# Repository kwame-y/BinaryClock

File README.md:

# TickTock — Pocket Binary Clock

A rechargeable pocket clock displaying **HH:MM:SS with 20 LEDs**, built around an ATtiny1616, a constant-current LED driver, and a real-time clock. Three edge-mounted buttons provide the planned MODE, PLUS, and MINUS controls, with USB-C for charging.

Designed in **KiCad 10**. This snapshot comes from **BinaryClock3**, with “TickTock REV 1.0” on the front silkscreen and a clock-face illustration on the back.

**Status: routed draft, not a manufacturing release.** The current checks report zero unconnected items and zero schematic-to-PCB parity issues, but electrical and design-rule violations remain. See [validation details](Hardware/VALIDATION.md).

## Schematic

The current schematic labels U4 as **BQ25186DLHR**. Its custom symbol and footprint identifiers still contain **BQ25185**; their suitability must be verified against the intended device before assembly. The earlier BQ24074 circuit is not included in this snapshot.

Open [Hardware/BinaryClock3.kicad_pro](Hardware/BinaryClock3.kicad_pro) in KiCad 10. Project-specific symbols, footprints, and available custom 3D models are included.

## Silkscreen

## PCB Layout

 · 

The saved board has **four copper layers** and a **1.6 mm thickness setting**. The plotted outline is approximately **60 × 30 mm**, larger than the original 50 × 30 mm target. Its saved appearance uses white front solder mask and blue back solder mask. The stackup currently specifies no copper finish; these settings need reconciliation with the intended manufacturing order.

The snapshot contains 334 track segments and 163 vias. These counts describe the saved design, not a fabrication approval.

## 3D Render

These are direct KiCad renders of the saved board. Some component bodies are absent because their 3D models are missing or unassigned; visible bare pads do not imply that those parts are omitted from the BOM.

## Bill of Materials

[Download BOM.csv](Production/BOM.csv), exported from the current schematic. It contains **52 component instances and 4 test points**. The external battery and thermistor are not included. Generic values and library names are not a complete purchasing specification; exact orderable parts, ratings, and pricing still need to be finalized.

| Reference | Value / part | Footprint | Quantity |
|---|---|---|---:|
| C1,C6,C7,C10 | 100nF | Capacitor_SMD:C_0402_1005Metric | 4 |
| C2 | 1µF | Capacitor_SMD:C_0603_1608Metric | 1 |
| C3 | 2.2µF | Capacitor_SMD:C_0603_1608Metric | 1 |
| C4,C5 | 10µF | Capacitor_SMD:C_0805_2012Metric | 2 |
| C11 | 1uF | Capacitor_SMD:C_0201_0603Metric | 1 |
| D1-D20 | RED | Custom Models:LED_APT1608LSECK_J3-PRV | 20 |
| J1 | USB4105-GF-A | Custom Models:USB4105_GCT | 1 |
| J2 | Conn_01x03 | Connector_JST:JST_SH_SM03B-SRSS-TB_1x03-1MP_P1.00mm_Horizontal | 1 |
| R1,R2 | 5.1kΩ | Resistor_SMD:R_0402_1005Metric | 2 |
| R3,R4 | 4.7kΩ | Resistor_SMD:R_0402_1005Metric | 2 |
| R5 | 47kΩ | Resistor_SMD:R_0402_1005Metric | 1 |
| R6,R7,R11 | 10kΩ | Resistor_SMD:R_0402_1005Metric | 3 |
| R8,R10,R12 | 100kΩ | Resistor_SMD:R_0402_1005Metric | 3 |
| R9 | 15kΩ | Resistor_SMD:R_0402_1005Metric | 1 |
| R14 | 1MΩ | Resistor_SMD:R_0402_1005Metric | 1 |
| R15 | 330kΩ | Resistor_SMD:R_0402_1005Metric | 1 |
| SW1-SW3 | SW_Push | Custom Models:SW_B3U-3000P | 3 |
| TP1 | UPDI | TestPoint:TestPoint_Pad_1.0x1.0mm | 1 |
| TP2 | SYS_PWR | TestPoint:TestPoint_Pad_1.0x1.0mm | 1 |
| TP3 | GND | TestPoint:TestPoint_Pad_1.0x1.0mm | 1 |
| TP4 | RTC_CLKOUT | TestPoint:TestPoint_Pad_1.0x1.0mm | 1 |
| U1 | ATtiny1616-M | Package_DFN_QFN:VQFN-20-1EP_3x3mm_P0.4mm_EP1.7x1.7mm | 1 |
| U2 | IS31FL3239-QFLS4-TR | Custom Models:QFN40P400X400X80-33N-D | 1 |
| U3 | RV-3028-C7 | Package_SON:MicroCrystal_C7_SON-8_1.5x3.2mm_P0.9mm | 1 |
| U4 | BQ25186DLHR | Custom Models:IC_BQ25185DLHR | 1 |

## Reading the Display

Each column represents one decimal digit. Add the weights of its illuminated LEDs to obtain that digit:

| Digit | Binary weights |
|---|---|
| Hour tens | 1, 2 |
| Hour units | 1, 2, 4, 8 |
| Minute tens | 1, 2, 4 |
| Minute units | 1, 2, 4, 8 |
| Second tens | 1, 2, 4 |
| Second units | 1, 2, 4, 8 |

## Repository Structure

```text
Hardware/
  BinaryClock3.kicad_pro
  BinaryClock3.kicad_sch
  BinaryClock3.kicad_pcb
  Custom_Libraries/
  3dmodels/
  reports/
  VALIDATION.md
Production/
  BOM.csv
images/
JOURNAL.md
README.md
```

The presentation follows [PCBCard](https://github.com/kwame-y/PCBCard). Backups, local editor state, and the source folder's history database are excluded.

## Remaining Work

- Resolve the ERC and DRC findings documented in the reports.
- Verify the charger symbol, physical pin mapping, and footprint against the intended part.
- Finalize the battery, connector polarity, and battery-temperature sensing arrangement.
- Confirm the final dimensions, stackup, finish, and assembly requirements.
- Implement and test firmware, including charger configuration and fault handling.
- Test an assembled prototype and enclosure fit before releasing production files.

## License

A project license has not yet been selected. Third-party symbols, footprints, and 3D models retain their original ownership and any applicable terms.

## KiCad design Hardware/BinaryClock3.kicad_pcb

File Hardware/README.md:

# Hardware

Open `BinaryClock3.kicad_pro` in **KiCad 10**. This is a snapshot of the saved BinaryClock3 project supplied on October 17, 2026.

The source schematic and project settings were copied byte-for-byte. The packaged PCB differs only in four 3D model path strings, changed to `${KIPRJMOD}/3dmodels/...` so those models travel with the project. No electrical connections, geometry, routing, or placement were changed. The original files remain untouched.

`Custom_Libraries` includes the four custom symbol definitions extracted from this schematic's embedded symbol cache and five footprint files copied from the adjacent Custom Models folder. The project library tables use relative paths. These are packaging operations, not validation of the custom parts. The board's embedded footprints remain authoritative for the saved layout; DRC reports two library-footprint mismatches.

Install the standard KiCad 10 symbol, footprint, and 3D-model libraries as well. Model assignments are incomplete in the saved design, so the included renders omit some component bodies.

`source-sha256.json` records the original three source-file hashes. `reports` contains the checks run on this packaged snapshot. See [VALIDATION.md](VALIDATION.md) before using it for fabrication.

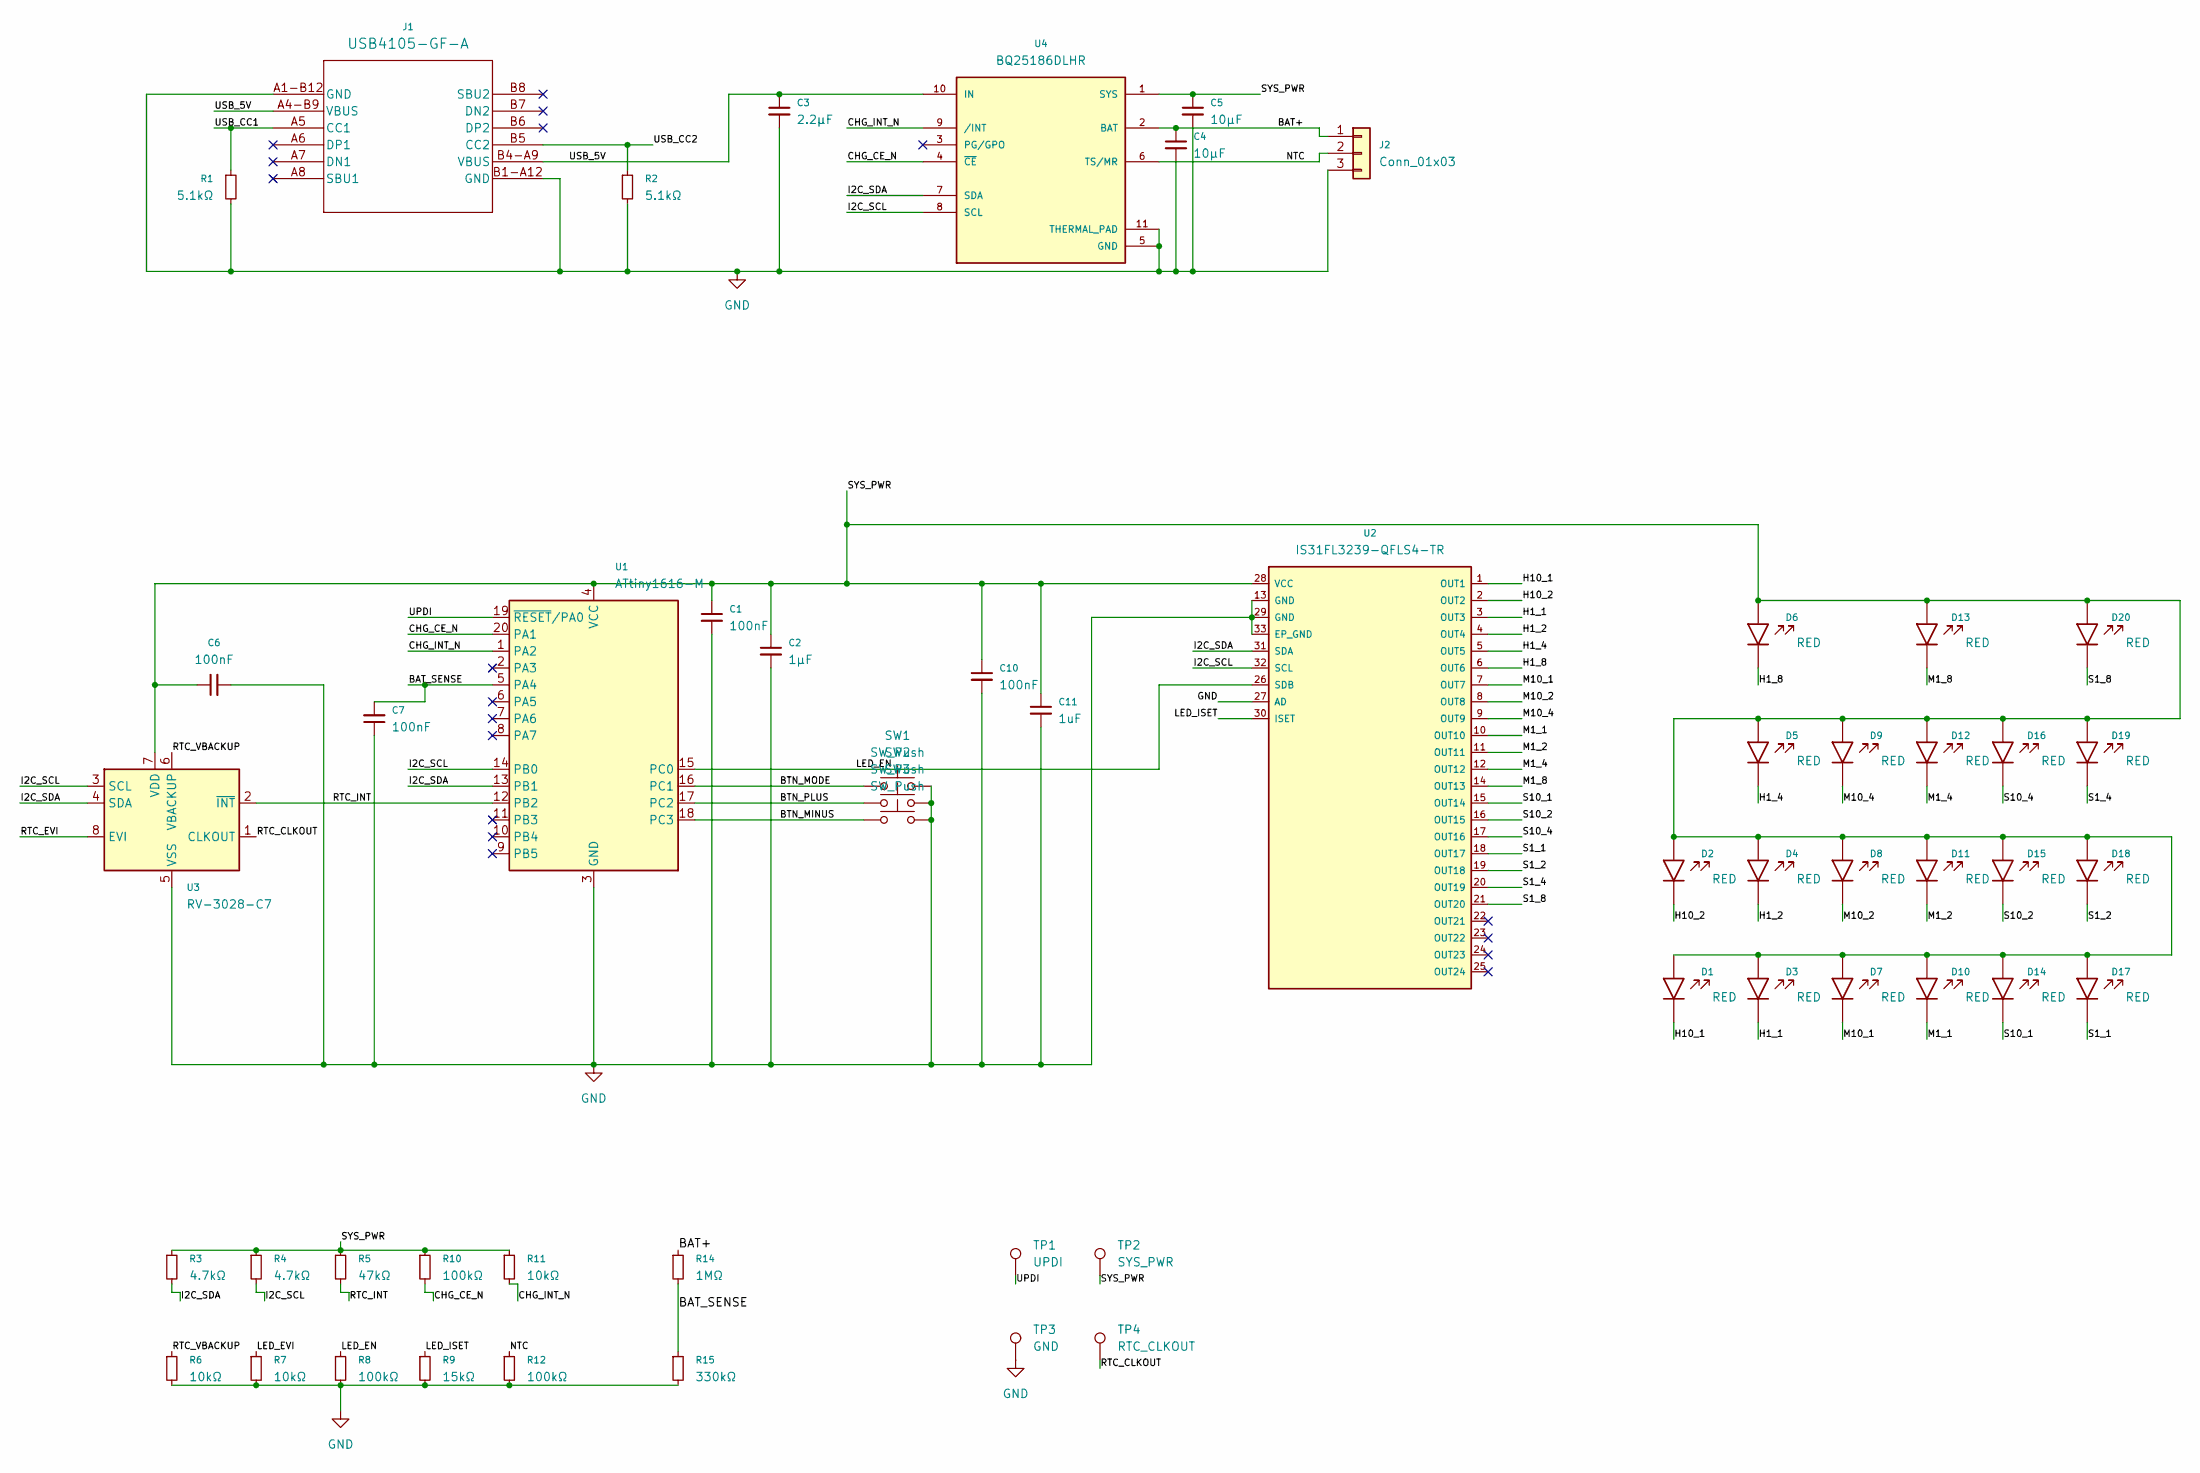
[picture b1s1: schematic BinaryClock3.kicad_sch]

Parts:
C1, C6, C7, C10: 100nF; C_0402_1005Metric
C2: 1µF; C_0603_1608Metric
C3: 2.2µF; C_0603_1608Metric
C4, C5: 10µF; C_0805_2012Metric
C11: 1uF; C_0201_0603Metric
D1, D2, D3, D4, D5, D6, D7, D8, D9, D10, D11, D12, D13, D14, D15, D16, D17, D18, D19, D20: RED; LED_APT1608LSECK_J3-PRV; MPN APT1608LSECK/J3-PRV
J1: USB4105-GF-A; USB4105_GCT
J2: Conn_01x03; JST_SH_SM03B-SRSS-TB_1x03-1MP_P1.00mm_Horizontal
R1, R2: 5.1kΩ; R_0402_1005Metric
R3, R4: 4.7kΩ; R_0402_1005Metric
R5: 47kΩ; R_0402_1005Metric
R6, R7, R11: 10kΩ; R_0402_1005Metric
R8, R10, R12: 100kΩ; R_0402_1005Metric
R9: 15kΩ; R_0402_1005Metric
R14: 1MΩ; R_0402_1005Metric
R15: 330kΩ; R_0402_1005Metric
SW1, SW2, SW3: SW_Push; SW_B3U-3000P
TP1: UPDI; TestPoint_Pad_1.0x1.0mm
TP2: SYS_PWR; TestPoint_Pad_1.0x1.0mm
TP3: GND; TestPoint_Pad_1.0x1.0mm
TP4: RTC_CLKOUT; TestPoint_Pad_1.0x1.0mm
U1: ATtiny1616-M; VQFN-20-1EP_3x3mm_P0.4mm_EP1.7x1.7mm
U2: IS31FL3239-QFLS4-TR; QFN40P400X400X80-33N-D; MPN IS31FL3239-QFLS4-TR
U3: RV-3028-C7; MicroCrystal_C7_SON-8_1.5x3.2mm_P0.9mm
U4: BQ25186DLHR; IC_BQ25185DLHR; PARTREV OCTOBER 2023

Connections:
/BAT+: C4.1, J2.1, R14.1, U4.2 (BAT)
/BAT_SENSE: C7.2, R14.2, R15.1, U1.5 (PA4)
/BTN_MINUS: SW3.1, U1.18 (PC3)
/BTN_MODE: SW1.1, U1.16 (PC1)
/BTN_PLUS: SW2.1, U1.17 (PC2)
/CHG_CE_N: R10.2, U1.20 (PA1), U4.4 (~CE)
/CHG_INT_N: R11.2, U1.1 (PA2), U4.9 (/INT)
/H1_1: D3.1 (K), U2.3 (OUT3)
/H1_2: D4.1 (K), U2.4 (OUT4)
/H1_4: D5.1 (K), U2.5 (OUT5)
/H1_8: D6.1 (K), U2.6 (OUT6)
/H10_1: D1.1 (K), U2.1 (OUT1)
/H10_2: D2.1 (K), U2.2 (OUT2)
/I2C_SCL: R4.2, U1.14 (PB0), U2.32 (SCL), U3.3 (SCL), U4.8 (SCL)
/I2C_SDA: R3.2, U1.13 (PB1), U2.31 (SDA), U3.4 (SDA), U4.7 (SDA)
/LED_EN: R8.1, U1.15 (PC0), U2.26 (SDB)
/LED_EVI: R7.1
/LED_ISET: R9.1, U2.30 (ISET)
/M1_1: D10.1 (K), U2.10 (OUT10)
/M1_2: D11.1 (K), U2.11 (OUT11)
/M1_4: D12.1 (K), U2.12 (OUT12)
/M1_8: D13.1 (K), U2.14 (OUT13)
/M10_1: D7.1 (K), U2.7 (OUT7)
/M10_2: D8.1 (K), U2.8 (OUT8)
/M10_4: D9.1 (K), U2.9 (OUT9)
/NTC: J2.2, R12.1, U4.6 (TS/MR)
/RTC_CLKOUT: TP4.1 (1_1), U3.1 (CLKOUT)
/RTC_EVI: U3.8 (EVI)
/RTC_INT: R5.2, U1.12 (PB2), U3.2 (~INT)
/RTC_VBACKUP: R6.1, U3.6 (VBACKUP)
/S1_1: D17.1 (K), U2.18 (OUT17)
/S1_2: D18.1 (K), U2.19 (OUT18)
/S1_4: D19.1 (K), U2.20 (OUT19)
/S1_8: D20.1 (K), U2.21 (OUT20)
/S10_1: D14.1 (K), U2.15 (OUT14)
/S10_2: D15.1 (K), U2.16 (OUT15)
/S10_4: D16.1 (K), U2.17 (OUT16)
/SYS_PWR: C1.1, C2.1, C5.1, C6.1, C10.1, C11.1, D1.2 (A), D2.2 (A), D3.2 (A), D4.2 (A), D5.2 (A), D6.2 (A), D7.2 (A), D8.2 (A), D9.2 (A), D10.2 (A), D11.2 (A), D12.2 (A), D13.2 (A), D14.2 (A), D15.2 (A), D16.2 (A), D17.2 (A), D18.2 (A), D19.2 (A), D20.2 (A), R3.1, R4.1, R5.1, R10.1, R11.1, TP2.1 (1_1), U1.4 (VCC), U2.28 (VCC), U3.7 (VDD), U4.1 (SYS)
/UPDI: TP1.1 (1_1), U1.19 (~RESET/PA0)
/USB_5V: C3.1, J1.A4-B9 (VBUS), J1.B4-A9 (VBUS), U4.10 (IN)
/USB_CC1: J1.A5 (CC1), R1.1
/USB_CC2: J1.B5 (CC2), R2.1
GND: C1.2, C2.2, C3.2, C4.2, C5.2, C6.2, C7.1, C10.2, C11.2, J1.A1-B12 (GND), J1.B1-A12 (GND), J2.3, R1.2, R2.2, R6.2, R7.2, R8.2, R9.2, R12.2, R15.2, SW1.2, SW2.2, SW3.2, TP3.1 (1_1), U1.3 (GND), U1.21 (GND), U2.13 (GND), U2.27 (AD), U2.29 (GND), U2.33 (EP_GND), U3.5 (VSS), U4.5 (GND), U4.11 (THERMAL_PAD)

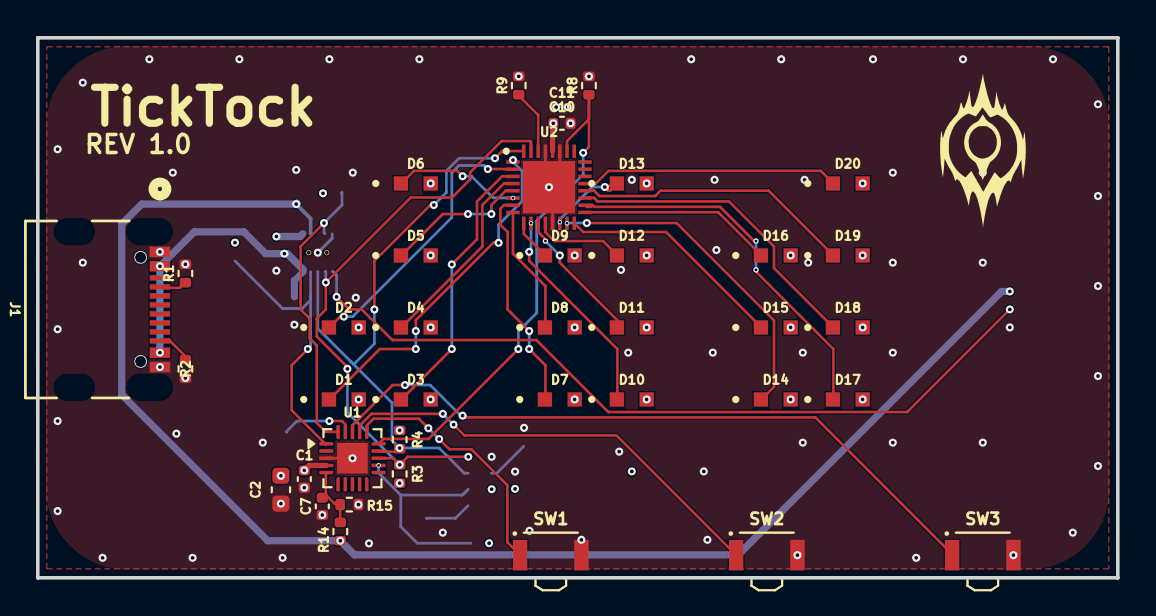
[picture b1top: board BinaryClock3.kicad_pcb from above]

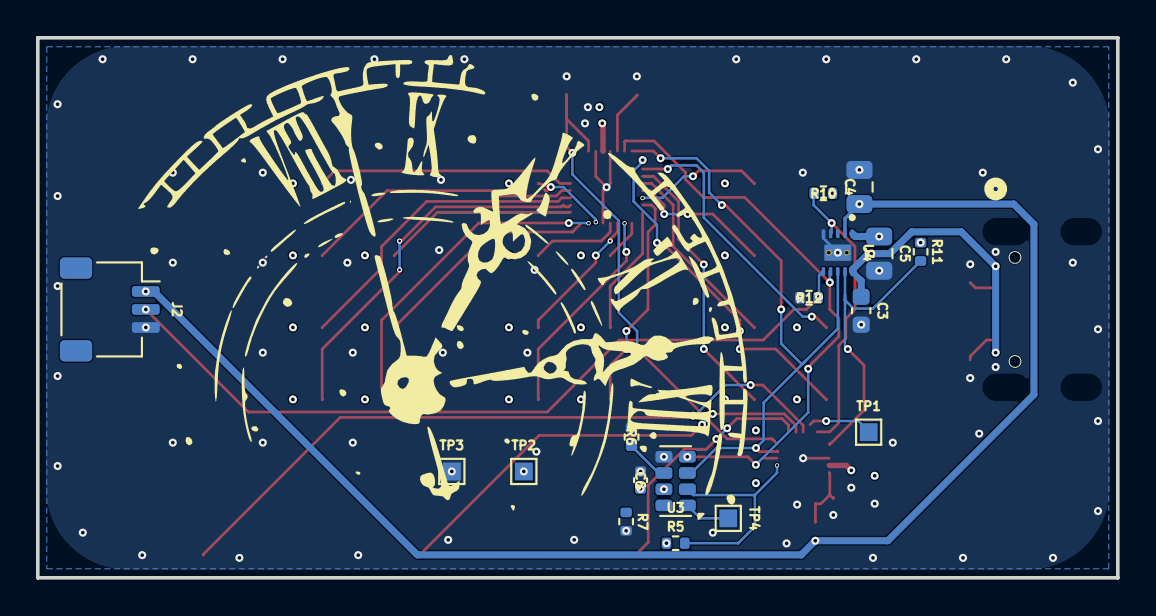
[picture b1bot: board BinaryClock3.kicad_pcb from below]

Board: 4 copper layers, 60.0 x 30.0 mm, 56 parts (17 on the bottom side), 41 nets.

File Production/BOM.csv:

"Refs","Value","Footprint","Qty","DNP"
"C1,C6,C7,C10","100nF","Capacitor_SMD:C_0402_1005Metric","4",""
"C2","1µF","Capacitor_SMD:C_0603_1608Metric","1",""
"C3","2.2µF","Capacitor_SMD:C_0603_1608Metric","1",""
"C4,C5","10µF","Capacitor_SMD:C_0805_2012Metric","2",""
"C11","1uF","Capacitor_SMD:C_0201_0603Metric","1",""
"D1-D20","RED","Custom Models:LED_APT1608LSECK_J3-PRV","20",""
"J1","USB4105-GF-A","Custom Models:USB4105_GCT","1",""
"J2","Conn_01x03","Connector_JST:JST_SH_SM03B-SRSS-TB_1x03-1MP_P1.00mm_Horizontal","1",""
"R1,R2","5.1kΩ","Resistor_SMD:R_0402_1005Metric","2",""
"R3,R4","4.7kΩ","Resistor_SMD:R_0402_1005Metric","2",""
"R5","47kΩ","Resistor_SMD:R_0402_1005Metric","1",""
"R6,R7,R11","10kΩ","Resistor_SMD:R_0402_1005Metric","3",""
"R8,R10,R12","100kΩ","Resistor_SMD:R_0402_1005Metric","3",""
"R9","15kΩ","Resistor_SMD:R_0402_1005Metric","1",""
"R14","1MΩ","Resistor_SMD:R_0402_1005Metric","1",""
"R15","330kΩ","Resistor_SMD:R_0402_1005Metric","1",""
"SW1-SW3","SW_Push","Custom Models:SW_B3U-3000P","3",""
"TP1","UPDI","TestPoint:TestPoint_Pad_1.0x1.0mm","1",""
"TP2","SYS_PWR","TestPoint:TestPoint_Pad_1.0x1.0mm","1",""
"TP3","GND","TestPoint:TestPoint_Pad_1.0x1.0mm","1",""
"TP4","RTC_CLKOUT","TestPoint:TestPoint_Pad_1.0x1.0mm","1",""
"U1","ATtiny1616-M","Package_DFN_QFN:VQFN-20-1EP_3x3mm_P0.4mm_EP1.7x1.7mm","1",""
"U2","IS31FL3239-QFLS4-TR","Custom Models:QFN40P400X400X80-33N-D","1",""
"U3","RV-3028-C7","Package_SON:MicroCrystal_C7_SON-8_1.5x3.2mm_P0.9mm","1",""
"U4","BQ25186DLHR","Custom Models:IC_BQ25185DLHR","1",""
